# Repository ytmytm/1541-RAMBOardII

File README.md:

# 1541-RAMBOard][

This is a recreation of [CLD RAMBoard](http://d81.de/CLD-RAMBOard/RAMBOard-2C.shtml) aimed at 1541-II drive with important change: 24K(32K) ROM support. It can be also configured to switch between two banks of 24K(32K) ROMs out of 64K ROM chip or one of four 16K banks.

It supports the following software:

- DolphinDOS2 using much fewer components than [original circuit](https://e4aws.silverdr.com/projects/dolphindos2/rev4/)
- software that needs extra 8K of RAM, such as Maverick
- patches for CBM DOS / JiffyDOS / SpeedDOS use extra ROM space to implement faster GCR decoding procedures from 1571 ROM
- patches also utilize drive RAM expansion to cache the current track

Note that for DolphinDOS 2 and SpeedDOS you need a [parallel connection](https://sta.c64.org/cbmpar41c.html) to C64/128 user port. Since the hardware side is the same, if you have no other reason to stick with SpeedDOS you should really go with DolphinDOS 2.

# Background

After completing [1571 RAM expansion](https://github.com/ytmytm/c128-bytewide-color-ram-1571cr-expansion) and providing [firmware patches for 1571](https://github.com/ytmytm/1571-TrackCacheROM) I turned my eyes to my two 1541-II drives, both already equipped with parallel cable, used in the past for [quick disk to disk copying](https://github.com/ytmytm/c64-ddbb).

I have checked out the [RAMBoard](http://d81.de/CLD-RAMBOard/RAMBOard-2C.shtml) but I wanted to use extra RAM as track cache and in original 1541 firmware there is just no space to put my patches. I would have to remove support for something, e.g. REL files.
So instead I redesigned the circuit to make it work in the following way:

- range `$8000-$9FFF` is RAM (8K)
- range `$A000-$BFFF` is ROM (8K)
- range `$C000-$FFFF` is ROM (16K)

This new 8K of ROM is the reason why from 32K ROM chip only 24K are visible for CPU - the first 8K being covered by RAM expansion.

I have spend few weeks working on original DOS code, JiffyDOS and SpeedDOS with invaluable help from [All About Your 1541](http://unusedino.de/ec64/technical/aay/c1541/).

It was at the very end of my work when I realized that this memory layout is *exactly* what is needed by DolphinDOS 2.

It seems my work on SpeedDOS was mostly a waste of time because DolphinDOS 2 does everything better and twice faster.

# Hardware

A stock 1541 disk drive has only 2K of SRAM in the range `$0000-$07FF`. This project provides at least 8K more.
It follows quite closely [RAMBoard](http://d81.de/CLD-RAMBOard/RAMBOard-2C.shtml) with the following changes:

- 32K SRAM (62256) is supported with jumpers for address lines A13/A14 that can be used for choosing 8K bank out of four possible
- 8K SRAM (6264) is also supported with extra wire (3rd PCB revision may improve on that)
- 32K/64K ROM (EPROM/EEPROM like 27C512) with two options
  - switch between two 32K banks (24K visible for CPU), for patched CBM DOS/JiffyDOS/SpeedDOS images or DolphinDOS 2
  - switch between four 16K banks for original 16K images of various DOS ROMs for 1541
- the board plugs into ROM socket and needs only two more signals from the mainboard

## Project

KiCad 6.0 project files are in [KiCad folder](kicad/1541-RAMBoard2-FirstBank/)

Schematic is [available as a PDF too](kicad/1541-RAMBoard2-FirstBank/plots/1541-RAMBoard2-FirstBank.pdf)

Gerber files for manufacturing are [available from plots folder](kicad/1541-RAMBoard2-FirstBank/plots/)

## Parts

- 2x 28 round goldpins to interconnect with onbooard ROM socket
- 2x DIP 28 sockets for new RAM and ROM
- 1x DIP 16 socket
- 1x 74LS139 (HC or HCT will work too)
- 10k resistors, depending on chosen configuration
- (if using 64K ROM) one or two switches to choose ROM
- 6264 or 62256 RAM
- 32K (27'256) or 64K (27'512) EPROM/EEPROM
- (for parallel connection) 10-wire flat cable

## Installation inside 1541-II

Due to height clearance in 1541-II it's not really possible to have the socket on mainboard and also on the daughterboard. The drive mechanism needs to be raised about 1-2mm for that, but then it's not possible to properly mount the front cover.

My recommendation is to make it process in steps:

1. assemble the 1541-RAMBOard][ daughterboard
2. open 1541-II case, remove ROM, install the board, connect two required wires
3. keep the case open, try your favourite software, check if everything works as expected
4. remove the ROM socket and solder the daughterboard in its place, directly to the mainboard

## Daughterboard assembly

1. Solder the pins that go down to the mainboard. Mind which set of holes is for pins.
2. Solder the two 28-pin sockets
3. Decide about the board setup - 2x24K(32K) or 4x16K ROMs
   a) for 2x24(32K) - close ROM_A14 jumper, install R15 resistor and a switch for ROM selection between ROM_A15 jumper (pin which connects to the resistor) and the ground
   b) for 4x16K - install R14 and R15 resistors and two switches for ROM selection between ROM_A14/ROM_A15 jumpers (both pins which connect to the resistors) and the ground
4. RAM_A13/A14 can be closed to keep them low for 32K SRAM (62256). **IMPORTANT NOTE** if you have 8K SRAM (6264) you **have to** keep RAM_A13 open and jumper pin that goes to RAM pin 26 to VCC. With 6264 that line is not A13 address line, but a `CE2` control signal that has to be kept high.

### Daughterboard initial installation

1. Remove original ROM from its socket
2. Push the daughterboard in its place, mind the orientation; chips on the dautherboard are oriented in the same way as those on the mainboard
3. Connect remaining two signals with wires to the mainboard
   a) A14 has to be connected to CPU (U3) pin 24
   b) R/W has to be connected to onboard RAM (U5) pin 21 or gate array (U10) pin 29 or 31 (depending on the board revision) or a very convenient via near R42 resistor. In any case check the connection to U5 pin 21!

Here is an example:

this board is configured for 8K 62256 RAM (both RAM_A13/A14 jumpers closed to GND) with two banks of 24K (32K) out of 64K EEPROM chip - R15 is installed, R14 is missing and ROM_A14 jumper is closed. There is no switch yet that would connect round pin of ROM_A15 to GND to select bottom half of EEPROM.

### Initial testing

You can put back original ROM into daughterboard. You don't need to install ROM selection switch for initial tests. By default the upper half of ROM will be selected for 64K ROM configured for 2x24K(32K) banks).

Your drive should start normally.

If you have Action Replay you can use its monitor to check if RAM works.

This command will read/write memory values from drive #8:
```
@*8
```
Now you can see the drive 8 RAM contents at address `$8000-8080`
```
M 8000 8080
```
Initial state of SRAM is usually random values. Use cursor up to run this command twice, the values should be stable.

Then try to edit some of them using typical testing bit patterns: `$00`, `$FF`, `$55`, `$AA`.

Run the `M` command once again to see if the values are still stable.

### Clearance considerations

Even though I ordered 0.8mm thick PCB the flywheel of drive mechanism was being blocked by the chips on the daughterboard.

I tried raising the front of mechanism about 1mm but then I couldn't install the front cover and close the case properly.

Since the board worked well and since it can be reconfigured back to 16K ROM at any time I decided to remove the onboard U4 ROM socket and solder the daughterboard directly to the mainboard.

Desoldering is easy with proper tool, but even with a soldering iron it's possible and not difficult if you first cut the socket in such way that you are working on one pin at a time. The holes can be cleared using a wooden toothpick.

Here is an example. U4 ROM socket has been removed, You can see R/W line (blue) and A14 (purple) already connected.

Before soldering in the daughterboard cover the nearby chips (U2 and U5) with a tape to prevent shorts. Don't forget about trimming all the pins from the daughterboard sockets and resistors as close as possible to the PCB also to prevent shortcuts.

In my case this way of installation was successful - I can still remove RAM and ROM from the sockets and there is no risk for the drive mechanism.

## Parallel cable

If you are going to use DolphinDOS 2 (highly recommended) it's also a good time for parallel cable installation.

1. On the solder side of the mainboard cut the trace between pins 1 and 2 of VIA#1 (U6)
2. Connect 10 wires of the flat cable in following way:

| **VIA#1 U6 pin** | **pin name** | **USER PORT** | **signal** | **Flat 10** |
| --- | --- | --- | --- | --- |
| 39  | CA2 | B   | /FLAG2 | 1 (red) |
| 2   | PA0 | C   | PB0 | 2   |
| 3   | PA1 | D   | PB1 | 3   |
| 4   | PA2 | E   | PB2 | 4   |
| 5   | PA3 | F   | PB3 | 5   |
| 6   | PA4 | H   | PB4 | 6   |
| 7   | PA5 | J   | PB5 | 7   |
| 8   | PA6 | K   | PB6 | 8   |
| 9   | PA7 | L   | PB7 | 9   |
| 18  | CB1 | 8   | /PC2 | 10  |

This makes it compatible with original [DolphinDOS 2 cable](https://e4aws.silverdr.com/resources/dolphindos2/dd2_schematic_rev4b-0.png) as well as the connector I provided for C128D on [Link232](https://github.com/ytmytm/c128-link232/blob/main/Swift-L%20(C128D)/plots/Link232-wifi.pdf).
 
# Software

## Copying software

Burst nibblers, such as Maverick, will be able to use extra RAM for copying data on GCR level.

RAM can be also confirmed using [ramboard.d64](doc/ramboard.d64) test disk.

## DolphinDOS 2

There is no configuration needed. These are stock ROM images, found on the Internet. Take them from (rom/)[rom/] folder:

- [C64 Kernal](rom/DolphinDOS2-Kernal-C64.rom)
- [C128 Kernal](rom/DolphinDOS2-Kernal-C128.rom)
- [1541-II](rom/DolphinDOS2-1541-II.bin)

I have put them also in the releases section.

## Configuration and assembly

(Note: if you want to try it out **now** just download one of the stock `...-patched.bin` files)

You need [KickAss](http://www.theweb.dk/KickAssembler/Main.html#frontpage) to assemble this code.

There is only one file here: [rampatch.asm](rampatch.asm). It reads a ROM as an input, applies patches and saves the result.

I have provided options for four stock images:

- original CBM DOS (251968-03)
- SpeedDOS 2.7 Plus (35 tracks) - C64 Kernal and corresponding 1541 ROM
- SpeedDOS 2.7 Plus+ (40 tracks) - C64 Kernal and corresponding 1541 ROM
- JiffyDOS 1541 (input ROM not provided here)

On the top of the [rampatch.asm](rampatch.asm) file there are configuration options:

- `RAMEXP` - the basis address of 8K area of expanded RAM, by default $8000 for $8000-$9FFF range
- uncomment one of the defines to choose which ROM image will be patched

Assemble the file to get patched ROM as a result. The ROM choice definition can also be passed on the command line:

```sh
java -jar <path-to>/KickAss.jar rampatch.asm -showmem -define ROMJIFFY1541II
```

Flash the result onto a 32K EEPROM and try it out.

Combine two 32K images to have more than one option within a 64K EEPROM.

In my case I have chosen to use JiffyDOS and DolphinDOS to have the best of both worlds.

### ROM API and firmware signature

Since the last update the patched 1541-II ROM now advertises a small, fixed-location API together with an identification signature:

* `$A000-$A002` – three-byte ASCII signature that lets host software confirm that the RAMBOard ][ firmware is active.
* `$A003`       – start of the public jump table. The first entry provides the SpeedDOS loader routine used by the patched C64 SpeedDOS Kernal

A patched C64 SpeedDOS Kernal will not waste time on uploading the drive code; it now jumps to the public API entry point at `$A003` instead.

# Results

There is no indication that the new code is in place. I didn't change the drive behaviour or RESET message. You can detect new ROM by checking the signature at `$A000`.

The SpeedDOS protocol loader is available in the 1541 ROM jump table at `$A003` and can be used by other platforms, like C16/116/+4 with parallel interface.

One thing that **will change** is the speed of **V**alidate command. You will hear that with the new ROM it's much faster, large files will be scanned with head moving across the tracks almost as fast as the format operation.

## Original CBM DOS

There is no functional change. GCR decoding routines are faster but data transfer is so slow that it doesn't matter. Older fastloaders that rely on ROM routines for loading sectors will be faster.

## JiffyDOS

Reading speed will be constantly over 10.5x instead of 9.8x no matter the sector interleave. The faster GCR decoding routines have some impact. Thanks to track cache the reading speed will be always the fastest possible, no matter if the files were saved with suboptimal original 1541 interleave (10) or the one preferred by JiffyDOS (6).

## SpeedDOS

Thanks to optimized GCR decoding and track cache, with parallel cable this is about three times faster than original SpeedDOS and almost as fast as Action Replay loader (about 16x). The patch on C64 side doesn't send any code to the drive anymore upon LOAD, it just executes the loader already within the drive ROM.

## DolphinDOS 2

Definietly the best solution. There is no competition to its 27x loading speed and improvements are in all operations (save, scratch, validate). I was able to fully confirm the benchmark results shown in [Comparison of fastloaders](https://www.c64-wiki.com/wiki/Comparison_of_fast_loaders).

## Is there any benefit?

Yes, if you use JiffyDOS and DolphinDOS 2. If parallel connection is available and there is no other important reason I wouldn't bother with SpeedDOS, when DolphinDOS is on the table.

This doesn't discount SpeedDOS loader that can be used by C16/116/+4 equipped with parallel interface.

# Theory of operation

The routines patch into:

- sector reading code
- GCR decoding (whole sector or just a buffer of 5 bytes)
- SpeedDOS loader

## Sector read

Any time a sector read is requested we check if that track is already cached. If it is cached then we decode cached GCR data into target buffer.

If requested track is not yet cached we read all the incoming data within one disk revolution. With 300rpm that will take 200ms. Any further reads from that track will come from the cache. The first 256 bytes go into buffers that start at $8000 and go up page by page. The remaining part (data and sector checksum) normally stored in work area $01BA-$01FF go into a sliding buffer in the upper section of the expanded RAM.

### Sector headers and disk revolution detection

Track reading starts with waiting for a sync signal and then for the first sector header. There is no time to decode the header at this moment so we just keep it as raw GCR in a buffer.

We also need to identify if a disk made a whole revolution already. This could be done by checking how many sectors we should expect, depending on the track number.

Instead I opted just for checking if the currently read header is the same as the very first one we saw.

### Housekeeping

Once the code detects that we already saw that sector header (or if it hits the limit of 23 sectors, which should never happen) we know that we saw a whole track.

We need to know in which order the sectors have been decoded, so now we need to decode all sector headers from GCR into binary and keep a list of their numbers. This way we know where to find that sector's data in the RAM expansion.

## GCR decoding

I have copied solution used by CBM in 1571 ROM. There are lookup tables used to quickly decode GCR into binary nibbles using only bit masking and lookups, without shifting bits. 1571 has 2MHz CPU clock and can use those tables while the data is coming from the disk, there is no time for that on 1541.
[There is a way to do it on the fly even on 1541](https://www.linusakesson.net/programming/gcr-decoding/index.php) but there is no time to move the data out of stack before the next sector. Either way it takes two disk revolutions to read+decode on the fly+move data or read+cache & decode later. (Although DolphinDOS 2 may prove me wrong).

## SpeedDOS loader

Original SpeedDOS LOAD handler used job codes to read data sector by sector. I changed it to read whole tracks and also handle the drive head movement in one routine, without going back to the original ROM. This made it about three times faster.

If you want to better understand how SpeedDOS LOAD works see [my commented disassembly](doc/speeddos40-loader.txt) of the code that is uploaded from C64 to the drive when a file is loaded.

A patched C64 Kernel will not waste time on uploading the code either, it will jump to the new ROM part in drive at `$A003` instead.

## Other patched routines

All the other patches are needed to indicate that the cache is no longer valid. This is done by putting $FF as the number of currently cached track.

These patches are applied on:

- the code that processes drive job commands to check if track has changed
- the code that runs after drive power-up or reset
- disk initialization 'I' command
- drive mode switching between 1541 and 1571 (`U0>M0` and `U0>M1`)

# Conclusions

No need to read further, just install that board with patched JiffyDOS and DolphinDOS ROMs and a switch.

A 1541 would be a very different product if the designers would provide at least one of the following:

- more RAM for track cache (1581)
- better serial transfer routines (JiffyDOS) or hardware serial (1571/81 burst)
- even better GCR decoding code or 2MHz clock to decode it on the fly (1571, DolphinDOS?)
- parallel connection (DolphinDOS)

A stock 1571 in tandem with C128 was a completely different experience.

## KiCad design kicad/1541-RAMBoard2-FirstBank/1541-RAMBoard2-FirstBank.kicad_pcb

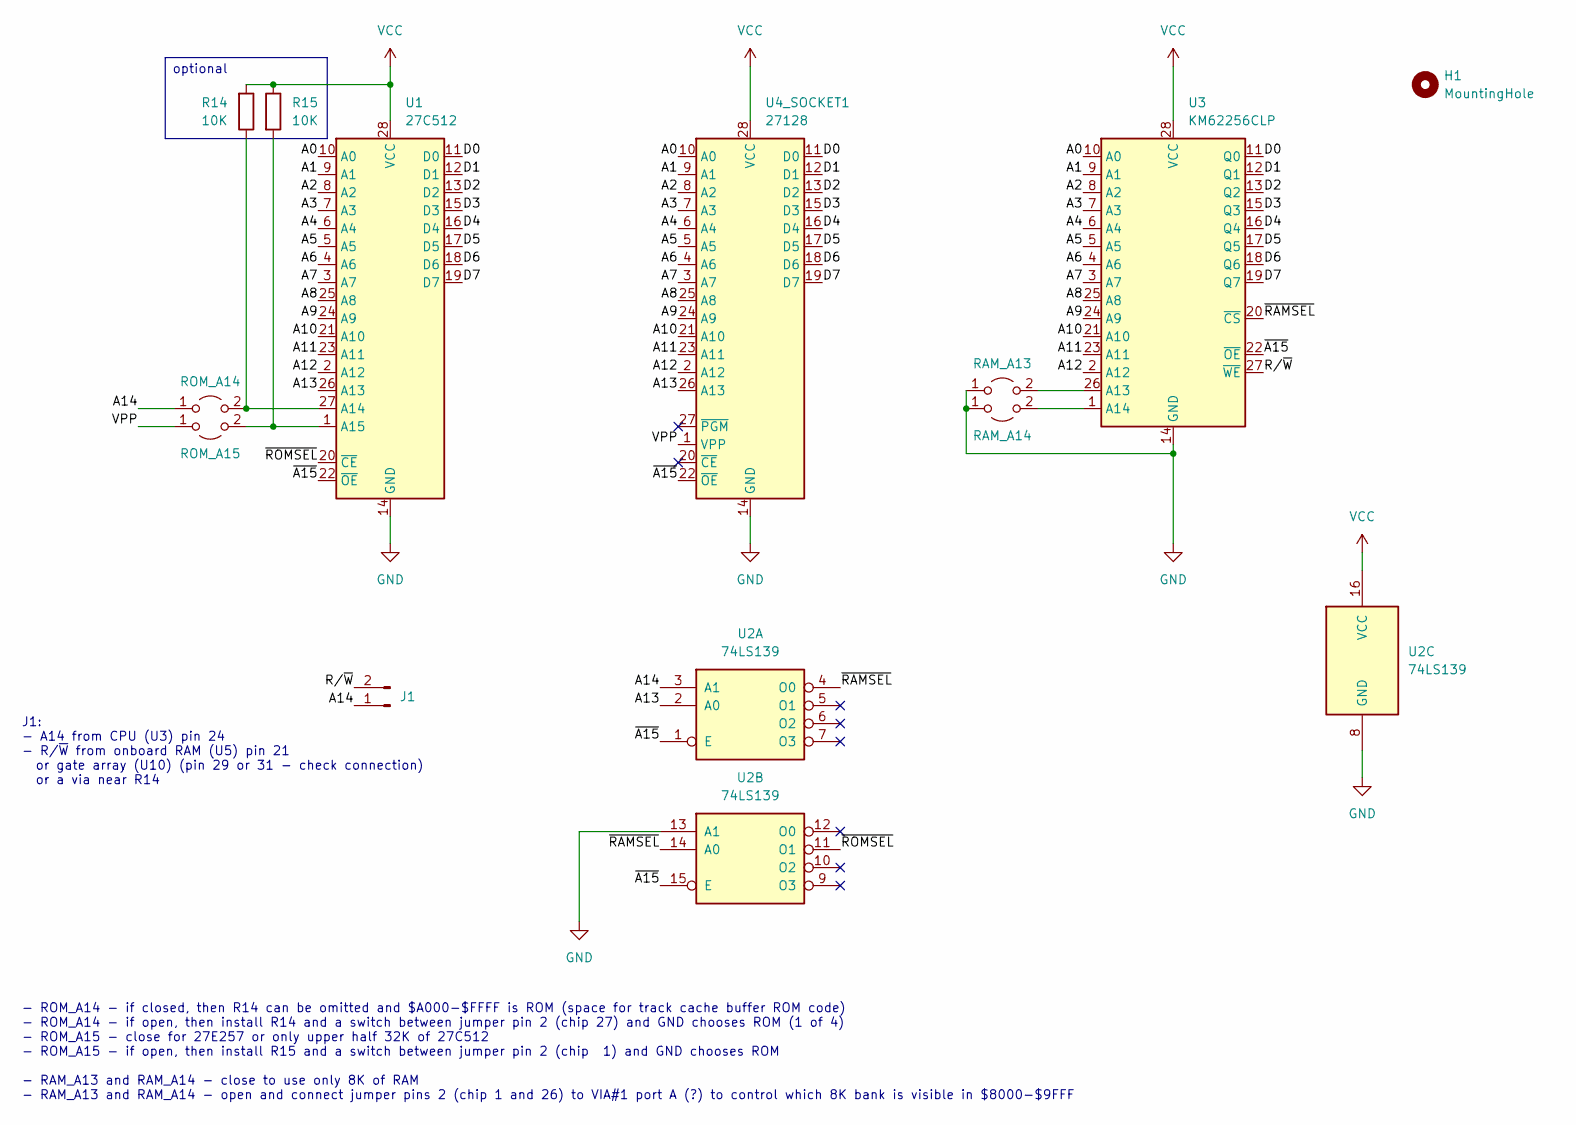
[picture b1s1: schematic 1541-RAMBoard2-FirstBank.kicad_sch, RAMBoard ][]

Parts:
H1: MountingHole; MountingHole_2.5mm
J1: Conn_01x02_Male; PinHeader_1x02_P2.54mm_Vertical
R14, R15: 10K; R_Axial_DIN0207_L6.3mm_D2.5mm_P7.62mm_Horizontal
RAM_A13: RAM_A13; PinHeader_1x02_P2.54mm_Vertical
RAM_A14: RAM_A14; PinHeader_1x02_P2.54mm_Vertical
ROM_A14: ROM_A14; PinHeader_1x02_P2.54mm_Vertical
ROM_A15: ROM_A15; PinHeader_1x02_P2.54mm_Vertical
U1: 27C512; DIP-28_W15.24mm_Socket_LongPads
U2: 74LS139; DIP-16_W7.62mm_Socket_LongPads
U3: KM62256CLP; DIP-28_W15.24mm_Socket_LongPads
U4_SOCKET1: 27128; DIP-28_W15.24mm_Socket_LongPads

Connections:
/A0: U1.10 (A0), U3.10 (A0), U4_SOCKET1.10 (A0)
/A1: U1.9 (A1), U3.9 (A1), U4_SOCKET1.9 (A1)
/A2: U1.8 (A2), U3.8 (A2), U4_SOCKET1.8 (A2)
/A3: U1.7 (A3), U3.7 (A3), U4_SOCKET1.7 (A3)
/A4: U1.6 (A4), U3.6 (A4), U4_SOCKET1.6 (A4)
/A5: U1.5 (A5), U3.5 (A5), U4_SOCKET1.5 (A5)
/A6: U1.4 (A6), U3.4 (A6), U4_SOCKET1.4 (A6)
/A7: U1.3 (A7), U3.3 (A7), U4_SOCKET1.3 (A7)
/A8: U1.25 (A8), U3.25 (A8), U4_SOCKET1.25 (A8)
/A9: U1.24 (A9), U3.24 (A9), U4_SOCKET1.24 (A9)
/A10: U1.21 (A10), U3.21 (A10), U4_SOCKET1.21 (A10)
/A11: U1.23 (A11), U3.23 (A11), U4_SOCKET1.23 (A11)
/A12: U1.2 (A12), U3.2 (A12), U4_SOCKET1.2 (A12)
/A13: U1.26 (A13), U2.2 (A0), U4_SOCKET1.26 (A13)
/A14: J1.1, ROM_A14.1 (A), U2.3 (A1)
/D0: U1.11 (D0), U3.11 (Q0), U4_SOCKET1.11 (D0)
/D1: U1.12 (D1), U3.12 (Q1), U4_SOCKET1.12 (D1)
/D2: U1.13 (D2), U3.13 (Q2), U4_SOCKET1.13 (D2)
/D3: U1.15 (D3), U3.15 (Q3), U4_SOCKET1.15 (D3)
/D4: U1.16 (D4), U3.16 (Q4), U4_SOCKET1.16 (D4)
/D5: U1.17 (D5), U3.17 (Q5), U4_SOCKET1.17 (D5)
/D6: U1.18 (D6), U3.18 (Q6), U4_SOCKET1.18 (D6)
/D7: U1.19 (D7), U3.19 (Q7), U4_SOCKET1.19 (D7)
/R/~W: J1.2, U3.27 (~WE)
/VPP: ROM_A15.1 (A), U4_SOCKET1.1 (VPP)
/~A15: U1.22 (~OE), U2.1 (E), U2.15 (E), U3.22 (~OE), U4_SOCKET1.22 (~OE)
/~RAMSEL: U2.4 (O0), U2.14 (A0), U3.20 (~CS)
/~ROMSEL: U1.20 (~CE), U2.11 (O1)
GND: RAM_A13.1 (A), RAM_A14.1 (A), U1.14 (GND), U2.8 (GND), U2.13 (A1), U3.14 (GND), U4_SOCKET1.14 (GND)
unnamed: R14.1, ROM_A14.2 (B), U1.27 (A14)
unnamed: R15.2, ROM_A15.2 (B), U1.1 (A15)
unnamed: RAM_A13.2 (B), U3.26 (A13)
unnamed: RAM_A14.2 (B), U3.1 (A14)
VCC: R14.2, R15.1, U1.28 (VCC), U2.16 (VCC), U3.28 (VCC), U4_SOCKET1.28 (VCC)

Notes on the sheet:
- ROM_A14 - if closed, then R14 can be omitted and $A000-$FFFF is ROM (space for track cache buffer ROM code) - ROM_A14 - if open, then install R14 and a switch between jumper pin 2 (chip 27) and GND chooses ROM (1 of 4) - ROM_A15 - close for 27E257 or only upper half 32K of 27C512 - ROM_A15 - if o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
J1: - A14 from CPU (U3) pin 24 - R/~{W} from onboard RAM (U5) pin 21 or gate array (U10) (pin 29 or 31 - check connection) or a via near R14
optional

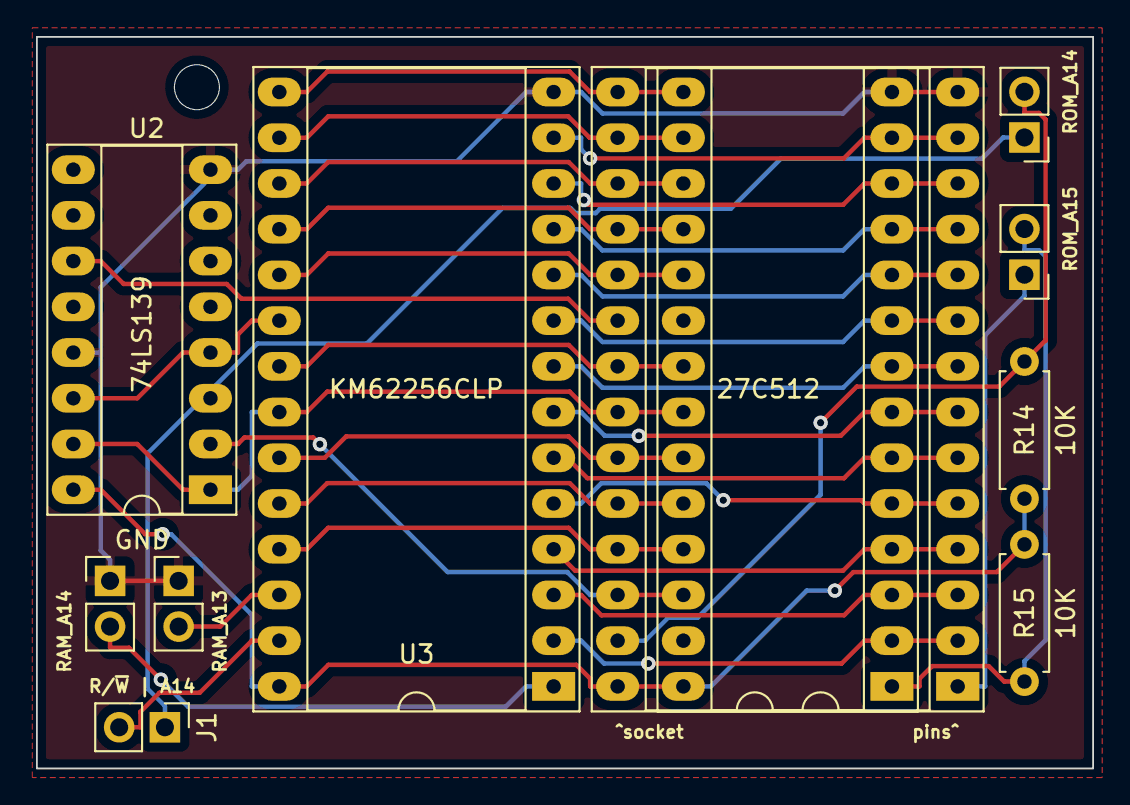
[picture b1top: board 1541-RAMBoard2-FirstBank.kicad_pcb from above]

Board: 2 copper layers, 58.7 x 40.6 mm, 12 parts (0 on the bottom side), 34 nets.

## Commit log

2024-04-10 initial commit, based off of https://github.com/ytmytm/1571-TrackCacheROM
2024-04-10 patch F8E0 / 9965 GCR decoding of whole sector using 1571 routine L98D9
2024-04-10 more comments, replace values by labels
2024-04-10 speed up header decoding, call L98D9 directly and only once per header to avoid copying data back and forth
2024-04-10 zero-copy sector decoding from cached GCR in expanded RAM into target buffer
2024-04-10 continued (version that almost is:) zero-copy sector decoding from cached GCR in expanded RAM into target buffer
2024-04-10 it seems this original 1571 code was wrong
2024-04-10 a guess why zero-copy GCR decoding doesn't work yet
2024-04-10 working zero-copy GCR sector decoder that reads cache and writes directly to target buffer; (problem was the original code assumption that (BUFPNT)+Y will not cross page boundary, so BUFPNT(lo byte) 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
2024-04-10 size optimization
2024-04-10 redirect F7E6 GCR decoding (5 bytes into 4) into our routine for faster processing even in some fastloaders
2024-04-10 be safe with parallel cable and don't set VIA#1 port A to output
2024-04-10 actually use these patches
2024-04-10 WIP: support for SpeedDOS 2.7/2.7+ - without Patch12 (port A as input), not needed here; but loaded data is wrong
2024-04-10 fix problem with SpeedDOS where first data sector wouldn't be right; they rely on $19 containing the sector number that was just read
2024-04-10 possible improvement?
2024-04-10 SpeedDOS support: patch C64 Kernal ROM to not upload drive code and jump into ROM procedure that will load data from track cache
2024-04-10 no need to read the very first sector, it's already there - the track is cached
2024-04-10 comments
2024-04-11 extract ReadCache into a subroutine, common for DOS and SpeedDOS; SpeedDOS checks for parity now
2024-04-11 SpeedDOS does honor ,8 and ,8,1 secondary address, it's transmitted over serial bus, so it's right that the parallel port funciton at f791 skips over it
2024-04-11 setup for JiffyDOS
2024-04-11 keep JiffyDOS out of git
2024-04-11 dissassembly of SpeedDos 2.7 / 2.7+ drive loader code
2024-04-11 correct case for 1541 CBM ROM
2024-04-11 cleanups
2024-04-14 port LFT's Spindle 3.1 to SpeedDOS LOAD handler; jams on track change
2024-04-15 correct stack handling within IRQ (track loading); speed dos finally faster than jiffydos
2024-04-15 load whole file within IRQ, head movement code from Spindle 3.1 but with fixed delay loop
2024-04-15 send last buffer on the track while the head is moving
2024-04-16 call SpeedDOS loader from IRQ, don't leave IRQ until end of the file; use own head move code (slow or fast)
2024-04-17 default for external assembly settings and true RAM address
2024-04-17 update comments
2024-04-17 drop unused definitions
2024-04-20 DolphinDOS2 is supported by this board(!)
2024-04-20 revision 1.1 - no changes except messages that R/W has to be connected to RAM (U6) R/W from gate array (U10), not directly to CPU R/W
2024-04-20 ramboard test program
2024-04-21 docs
2024-04-22 media files
2024-04-22 bring in patched ROMs
2024-04-22 diary
2024-04-22 implement CI for release artifacts
2024-04-22 initial port of LFT's GCR on the fly decoder from Spindle 3.1 ; https://www.linusakesson.net/programming/gcr-decoding/index.php
2024-04-22 save only up to possible stack pointer
2024-04-22 save only between stack pointer and max possible stack pointer (reduces best interleave from 6 to 5, improvement on JiffyDOS)
2025-07-05 make SpeedDOSLoader and other new functions available as a jumptable at 0xA003 with signature at 0xA000
2025-07-06 Update GitHub Actions workflow to use actions/checkout@v4 and actions/upload-artifact@v4
